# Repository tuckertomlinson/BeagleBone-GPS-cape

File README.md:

PCB layout for a GPS cape for the beaglebone black.

This is a home project. There is NO garauntee that the circuits do what
is intended, or that the function is adequately documented.

Any use of the files found in this project should be accompanied by a 
thorough review to determine proper function and fitness for use.

Project goals:
- clock discipline for the Beaglebone family such that a beaglebone with cape
	may act as an NTP stratum1 timeserver on a local network
- Use a GPS module to generate a 1 PPS signal that is synced to the atomic 
	clocks. The GPS module should interface with an active antenna so that
	good satellite lock may be attained indoors.
- provide an accurate RTC via a stand-alone i2c RTC module
- Hardware will be provided on a PCB cape, using SMT components for tight layout
	and low cost.
- Provide a hardware overlay file that may be enabled in uEnv.txt that will 
	automatically configure the correct pins for PPS capture, and RTC 
	connection

Stretch goals:
- Included a voltage regulated clock source, and force the BB to use the external 
	clock for better frequency stability

Current status:
- Proof of concept based on Adafruit Ultimate GPS breakout constructed and working
- 2 hardware capes designed
	- low cost cape based on Sierra Wireless XM1100 module
		- includeds RTC, and active antenna circuit
	- High cost cape based on uBlox LEA-M8T module
		- includes RTC, and 24Mhz VCTCXO clock. 
		- GPS module provides active antenna power
- Capes use Uart 4 to recieve GPS packets, and timer4 to take in PPS
- RTC is on i2c 1

Both capes completely untested.

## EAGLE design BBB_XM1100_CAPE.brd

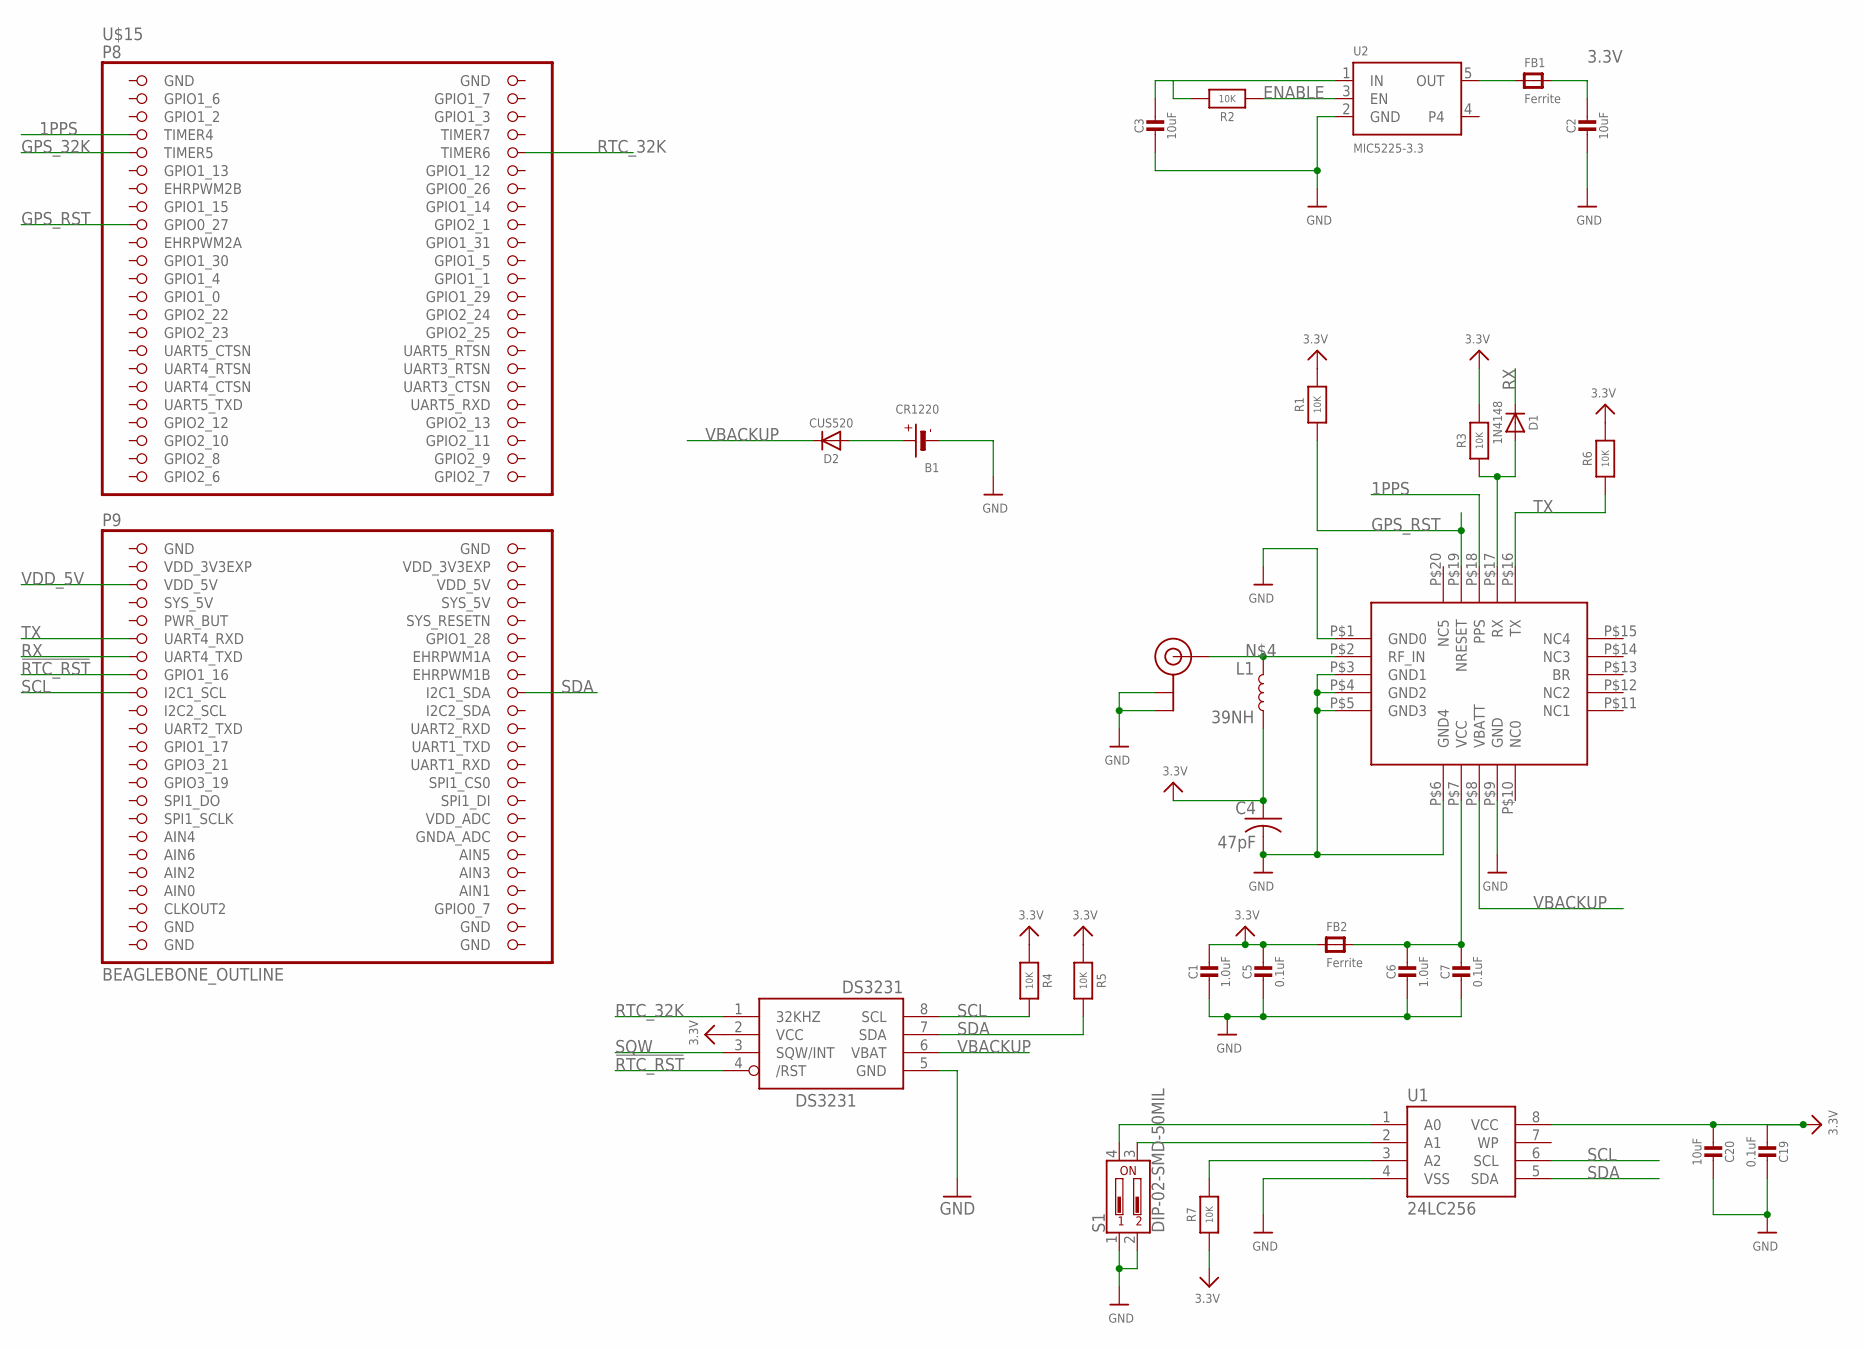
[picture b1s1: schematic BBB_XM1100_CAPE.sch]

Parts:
B1: CR1220
C1, C6: 1.0uF; 0805-NO
C2, C3, C20: 10uF; 0805-NO
C4: 47pF; C0805
C5, C7, C19: 0.1uF; 0805-NO
D1: 1N4148; SOD-323
D2: CUS520; SOD-323
DS3231: DS3231M-8PIN; SO08
FB1, FB2: Ferrite; 0805-NO@1
L1: 39NH; 0402
R1, R2, R3, R4, R5, R6, R7: 10K; 0805-NO
S1: DIP-02-SMD-50MIL; DIPSWITCH-02-50MIL
U1: 24LC256; SO08
U2: MIC5225-3.3; SOT23-5
U$3: XM1100
U$15: BEAGLEBONE_OUTLINE; BEAGLEBONE_SHIELD
U$20: U.FL

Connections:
1PPS: U$3.P$18 (PPS), U$15.7 (TIMER4)
3.3V: C1.1, C2.1, C4.1, C5.1, C19.1, C20.1, DS3231.2 (VCC), FB1.2, FB2.1, L1.2, R1.1, R3.1, R4.1, R5.1, R6.1, R7.1, U1.8 (VCC)
!RTC_RST: DS3231.4 (/RST), U$15.61 (GPIO1_16)
AIN0: U$15.85 (AIN0)
ENABLE: R2.1, U2.3 (EN)
GND: B1.-, C1.2, C2.2, C3.2, C4.2, C5.2, C6.2, C7.2, C19.2, C20.2, DS3231.5 (GND), S1.1, S1.2, U1.4 (VSS), U2.2 (GND), U$3.P$1 (GND0), U$3.P$3 (GND1), U$3.P$4 (GND2), U$3.P$5 (GND3), U$3.P$6 (GND4), U$3.P$9 (GND), U$15.1 (GND), U$15.2 (GND), U$15.47 (GND), U$15.48 (GND), U$15.89 (GND), U$15.90 (GND), U$15.91 (GND), U$15.92 (GND), U$20.P$1 (GND), U$20.P$2 (GND)
GPS_32K: U$15.9 (TIMER5)
GPS_RST: R1.2, U$3.P$19 (NRESET), U$15.17 (GPIO0_27)
unnamed: B1.+$1 (+), D2.A
unnamed: FB1.1, U2.5 (OUT)
unnamed: L1.1, U$3.P$2 (RF_IN), U$20.P$3 (SIGNAL)
unnamed: C6.1, C7.1, FB2.2, U$3.P$7 (VCC)
unnamed: R7.2, U1.3 (A2)
unnamed: S1.3, U1.2 (A1)
unnamed: S1.4, U1.1 (A0)
RTC_32K: DS3231.1 (32KHZ), U$15.10 (TIMER6)
RX: D1.C, U$15.59 (UART4_TXD)
RX_3V: D1.A, R3.2, U$3.P$17 (RX)
SCL: DS3231.8 (SCL), R4.2, U1.6 (SCL), U$15.63 (I2C1_SCL)
SDA: DS3231.7 (SDA), R5.2, U1.5 (SDA), U$15.64 (I2C1_SDA)
SQW: DS3231.3 (SQW/INT)
SYS_5V: U$15.53 (SYS_5V)
TX: R6.2, U$3.P$16 (TX), U$15.57 (UART4_RXD)
VBACKUP: D2.C, DS3231.6 (VBAT), U$3.P$8 (VBATT)
VDD_3V3EXP: U$15.49 (VDD_3V3EXP), U$15.50 (VDD_3V3EXP)
VDD_5V: C3.1, R2.2, U2.1 (IN), U$15.51 (VDD_5V), U$15.52 (VDD_5V)

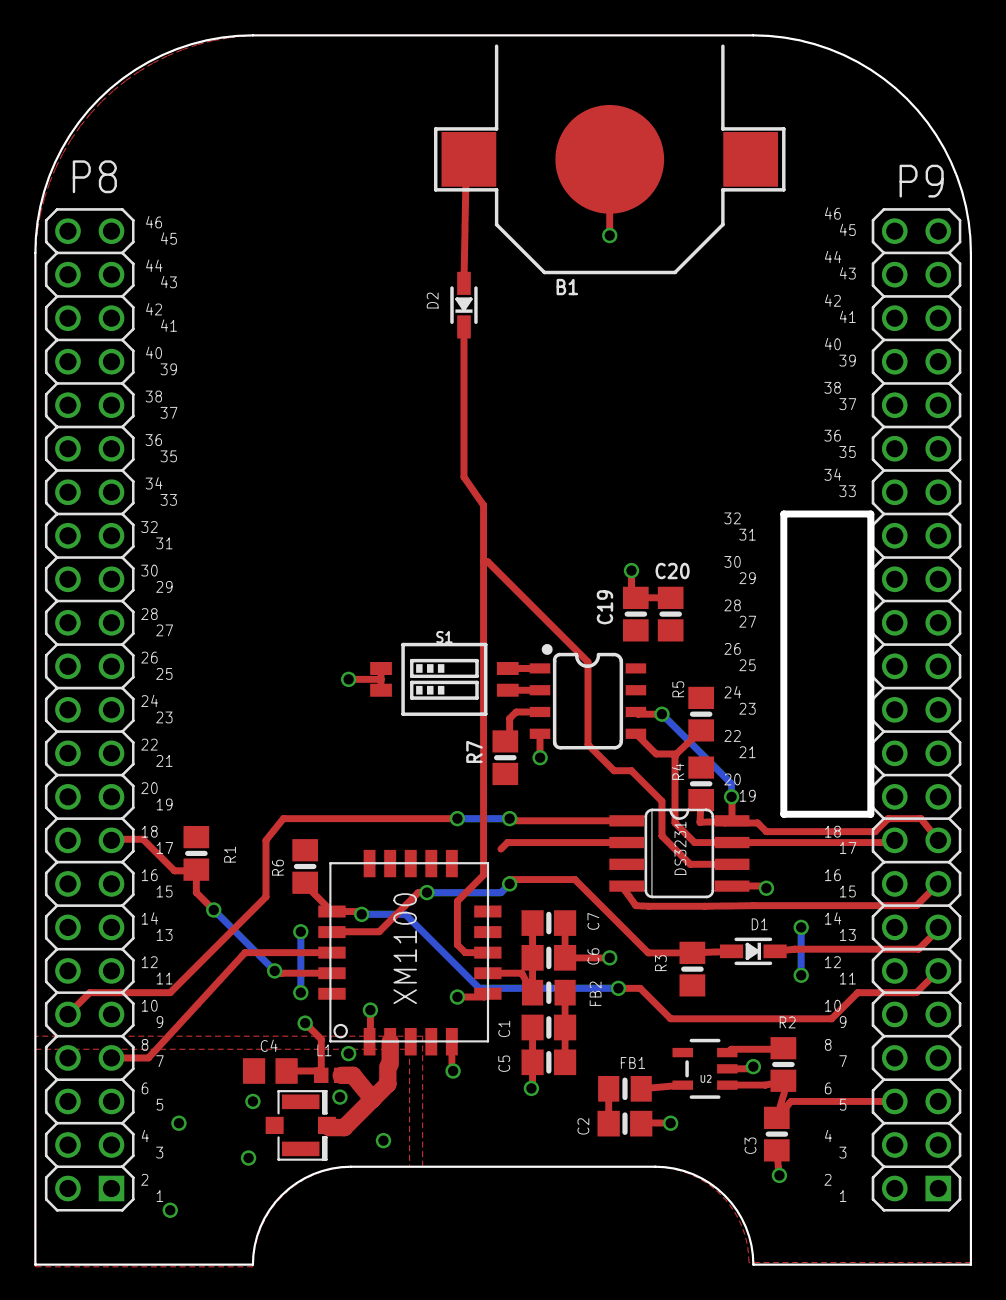
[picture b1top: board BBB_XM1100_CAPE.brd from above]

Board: 2 copper layers, 54.3 x 71.5 mm, 29 parts (0 on the bottom side), 22 nets.

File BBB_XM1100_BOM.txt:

BeagleBone LEA-M8T GPS timing cape BOM:
notes: 
1)almost no effort was given here to cost optimization. Caps and resistors may likely be substituted for alternative components at lower cost. 
2)cost reflects prices on Digikey as of the time that this BOM was compiled. Prices reflect single part quantity. discounts for bulk purchases are not taken into account

part: 			board ID			manuf		manuf. #		digikey#		cost Apr 2018 	link
GPS module		U$3				Sierra		XXM1100_1103874		 1645-1040-1-ND 	$12.98		https://www.digikey.com/product-detail/en/sierra-wireless/XM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		
10uF cap 0805		C1,C2,C3,C6			TDK		C2012X7R1A106K125AE 	445-173616-1-ND		$0.46		https://www.digikey.com/product-detail/en/tdk-corporation/C2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
0.1uF cap 0805		C5,C7				TDK		CGA4J2X8R1H104K125AA 	445-5909-1-ND 		$0.22		https://www.digikey.com/product-detail/en/tdk-corporation/CG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
47pF cap 0805		C4				ATC		600F470FT250XT  	1284-1061-1-ND 		$2.25		https://www.digikey.com/product-detail/en/american-technical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	
10kohm Resistor 0805	R1,R2,R3,R4,R5			Panasonic	ERA-6AEB103V		P10KDACT-ND 		$0.36		https://www.digikey.com/product-detail/en/panasonic-electron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
10 ohm Resistor 0805	R6				Vishay		TNPW080510R0FEEA	541-3916-1-ND 		$0.42		https://www.digikey.com/product-detail/en/vishay-dale/TNPW08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
Ferrite bead	0805	FB1,FB2				Laird		HI0805O121R-10		240-2393-1-ND		$0.11		https://www.digikey.com/product-detail/en/laird-signal-integ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
39nH inductor 0805	L1				Abracon		AISC-0805HQ-39NJ-T	535-12362-1-ND		$0.40		https://www.digikey.com/product-detail/en/murata-electronics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
3.3V regulator		U2				Microchip 	MIC5225-3.3		576-2980-1-ND 		$0.41		https://www.digikey.com/product-detail/en/microchip-technolo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
RTC			DS3231				Maxim		Ds3231MZ+		DS3231MZ+-ND		$7.72		https://www.digikey.com/product-detail/en/maxim-integrated/D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
U.FL Antenna jack	U$20				TE Connectivity	1909763-1 		 A118077CT-ND		$0.49		https://www.digikey.com/product-detail/en/te-connectivity-am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	
2X pinhdr 2x23		U$15				Samtec		SSQ-123-03-G-D		SAM1196-23-ND		$9.11		https://www.digikey.com/product-detail/en/samtec-inc/SSQ-123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  alt: https://www.adafruit.com/product/706
Diode			D1				Diodes Inc	1N4148WS-7-F		1N4148WS-FDICT-ND	$0.19		https://www.digikey.com/product-detail/en/diodes-incorporate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
Diode			D2				Toshiba		CUS520,H3F		CUS520H3FCT-ND		$0.22		https://www.digikey.com/product-detail/en/toshiba-semiconduc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
CR1220 batt. holder	B1				MPD		BK-885 			BK-885-ND		$0.35		https://www.digikey.com/products/en?keywords=3001k-nd

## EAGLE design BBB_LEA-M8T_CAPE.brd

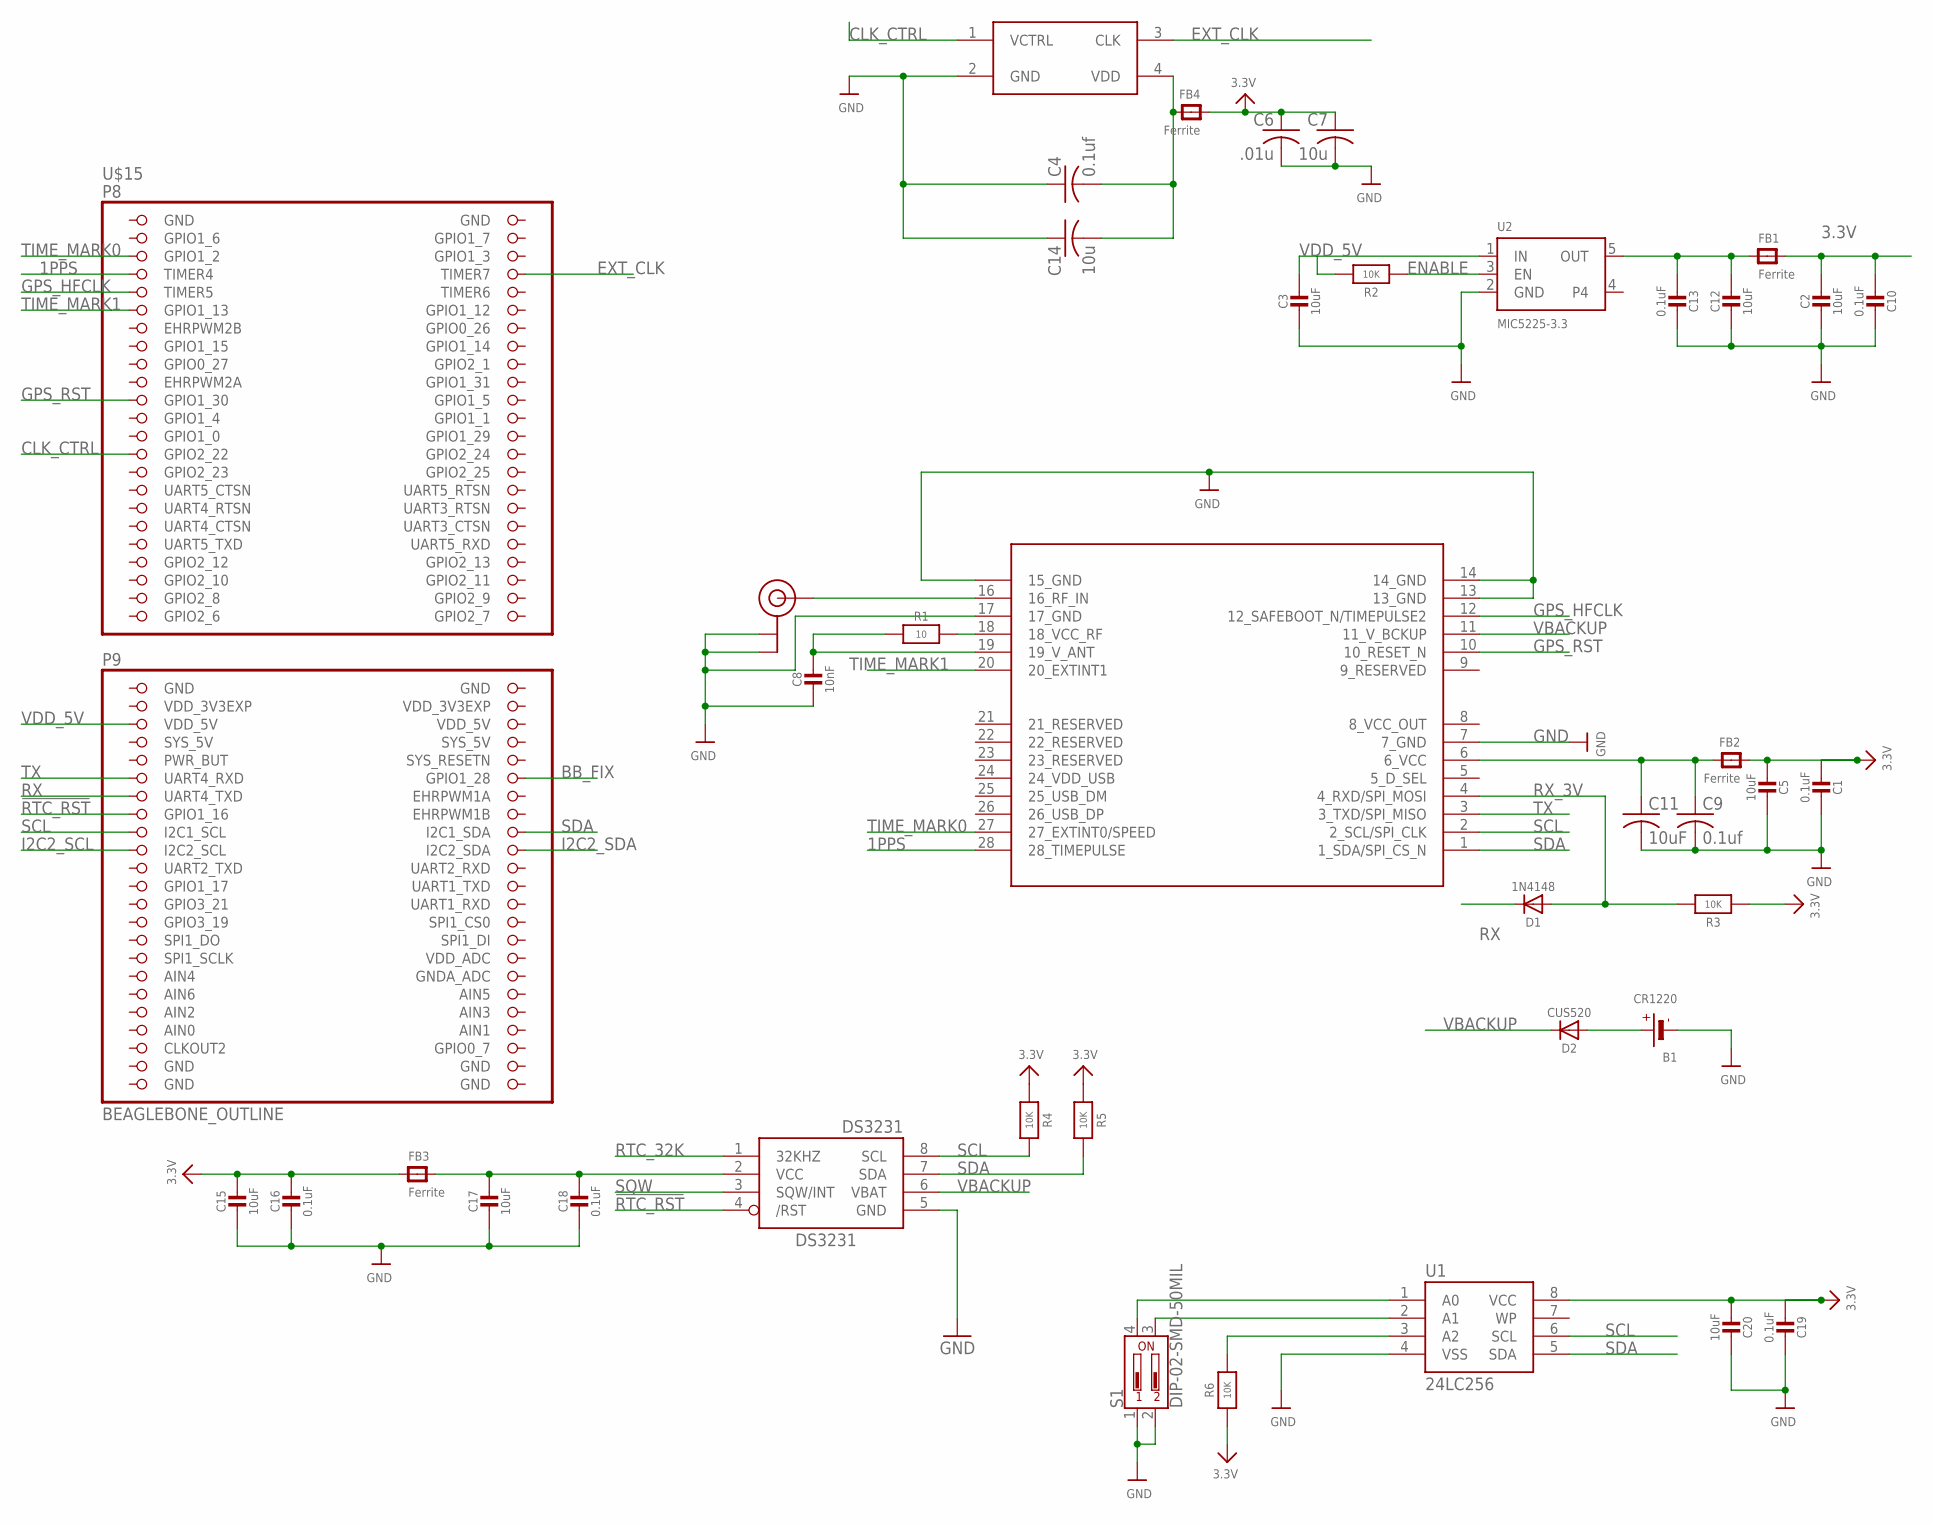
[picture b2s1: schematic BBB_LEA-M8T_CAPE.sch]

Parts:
B1: CR1220
C1, C10, C13, C16, C18, C19: 0.1uF; 0805-NO
C2, C3, C5, C12, C15, C17, C20: 10uF; 0805-NO
C4, C9: 0.1uf; C0805
C6: .01u; C0805
C7, C14: 10u; C0805
C8: 10nF; 0805-NO
C11: 10uF; C0805
D1: 1N4148; SOD-323
D2: CUS520; SOD-323
DS3231: DS3231M-8PIN; SO08
FB1, FB2, FB3, FB4: Ferrite; 0805-NO@1
R1: 10; 0805-NO
R2, R3, R4, R5, R6: 10K; 0805-NO
S1: DIP-02-SMD-50MIL; DIPSWITCH-02-50MIL
U1: 24LC256; SO08
U2: MIC5225-3.3; SOT23-5
U$1: LEA-M8
U$3: TAITIEN_TW-SERIES_OSCILLATOR
U$15: BEAGLEBONE_OUTLINE; BEAGLEBONE_SHIELD
U$20: U.FL

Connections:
1PPS: U$1.28 (28_TIMEPULSE), U$15.7 (TIMER4)
3.3V: C1.1, C2.1, C5.1, C6.1, C7.1, C10.1, C15.1, C16.1, C19.1, C20.1, FB1.2, FB2.1, FB3.1, FB4.1, R3.1, R4.1, R5.1, R6.1, U1.8 (VCC)
!RTC_RST: DS3231.4 (/RST), U$15.61 (GPIO1_16)
AIN0: U$15.85 (AIN0)
BB_FIX: U$15.58 (GPIO1_28)
CLK_CTRL: U$3.1 (VCTRL), U$15.27 (GPIO2_22)
ENABLE: R2.1, U2.3 (EN)
EXT_CLK: U$3.3 (CLK), U$15.8 (TIMER7)
GND: B1.-, C1.2, C2.2, C3.2, C4.1, C5.2, C6.2, C7.2, C8.2, C9.2, C10.2, C11.2, C12.2, C13.2, C14.1, C15.2, C16.2, C17.2, C18.2, C19.2, C20.2, DS3231.5 (GND), S1.1, S1.2, U1.4 (VSS), U2.2 (GND), U$1.7 (7_GND), U$1.13 (13_GND), U$1.14 (14_GND), U$1.15 (15_GND), U$1.17 (17_GND), U$3.2 (GND), U$15.1 (GND), U$15.2 (GND), U$15.47 (GND), U$15.48 (GND), U$15.89 (GND), U$15.90 (GND), U$15.91 (GND), U$15.92 (GND), U$20.P$1 (GND), U$20.P$2 (GND)
GPS_HFCLK: U$1.12 (12_SAFEBOOT_N/TIMEPULSE2), U$15.9 (TIMER5)
GPS_RST: U$1.10 (10_RESET_N), U$15.21 (GPIO1_30)
I2C2_SCL: U$15.65 (I2C2_SCL)
I2C2_SDA: U$15.66 (I2C2_SDA)
unnamed: B1.+$1 (+), D2.A
unnamed: C9.1, C11.1, FB2.2, U$1.6 (6_VCC)
unnamed: C12.1, C13.1, FB1.1, U2.5 (OUT)
unnamed: U$1.16 (16_RF_IN), U$20.P$3 (SIGNAL)
unnamed: C4.2, C14.2, FB4.2, U$3.4 (VDD)
unnamed: C17.1, C18.1, DS3231.2 (VCC), FB3.2
unnamed: R6.2, U1.3 (A2)
unnamed: S1.3, U1.2 (A1)
unnamed: S1.4, U1.1 (A0)
unnamed: R1.2, U$1.18 (18_VCC_RF)
unnamed: C8.1, R1.1, U$1.19 (19_V_ANT)
RTC_32K: DS3231.1 (32KHZ)
RX: D1.C, U$15.59 (UART4_TXD)
RX_3V: D1.A, R3.2, U$1.4 (4_RXD/SPI_MOSI)
SCL: DS3231.8 (SCL), R4.2, U1.6 (SCL), U$1.2 (2_SCL/SPI_CLK), U$15.63 (I2C1_SCL)
SDA: DS3231.7 (SDA), R5.2, U1.5 (SDA), U$1.1 (1_SDA/SPI_CS_N), U$15.64 (I2C1_SDA)
SQW: DS3231.3 (SQW/INT)
SYS_5V: U$15.53 (SYS_5V)
TIME_MARK0: U$1.27 (27_EXTINT0/SPEED), U$15.5 (GPIO1_2)
TIME_MARK1: U$1.20 (20_EXTINT1), U$15.11 (GPIO1_13)
TX: U$1.3 (3_TXD/SPI_MISO), U$15.57 (UART4_RXD)
VBACKUP: D2.C, DS3231.6 (VBAT), U$1.11 (11_V_BCKUP)
VDD_3V3EXP: U$15.49 (VDD_3V3EXP), U$15.50 (VDD_3V3EXP)
VDD_5V: C3.1, R2.2, U2.1 (IN), U$15.51 (VDD_5V), U$15.52 (VDD_5V)

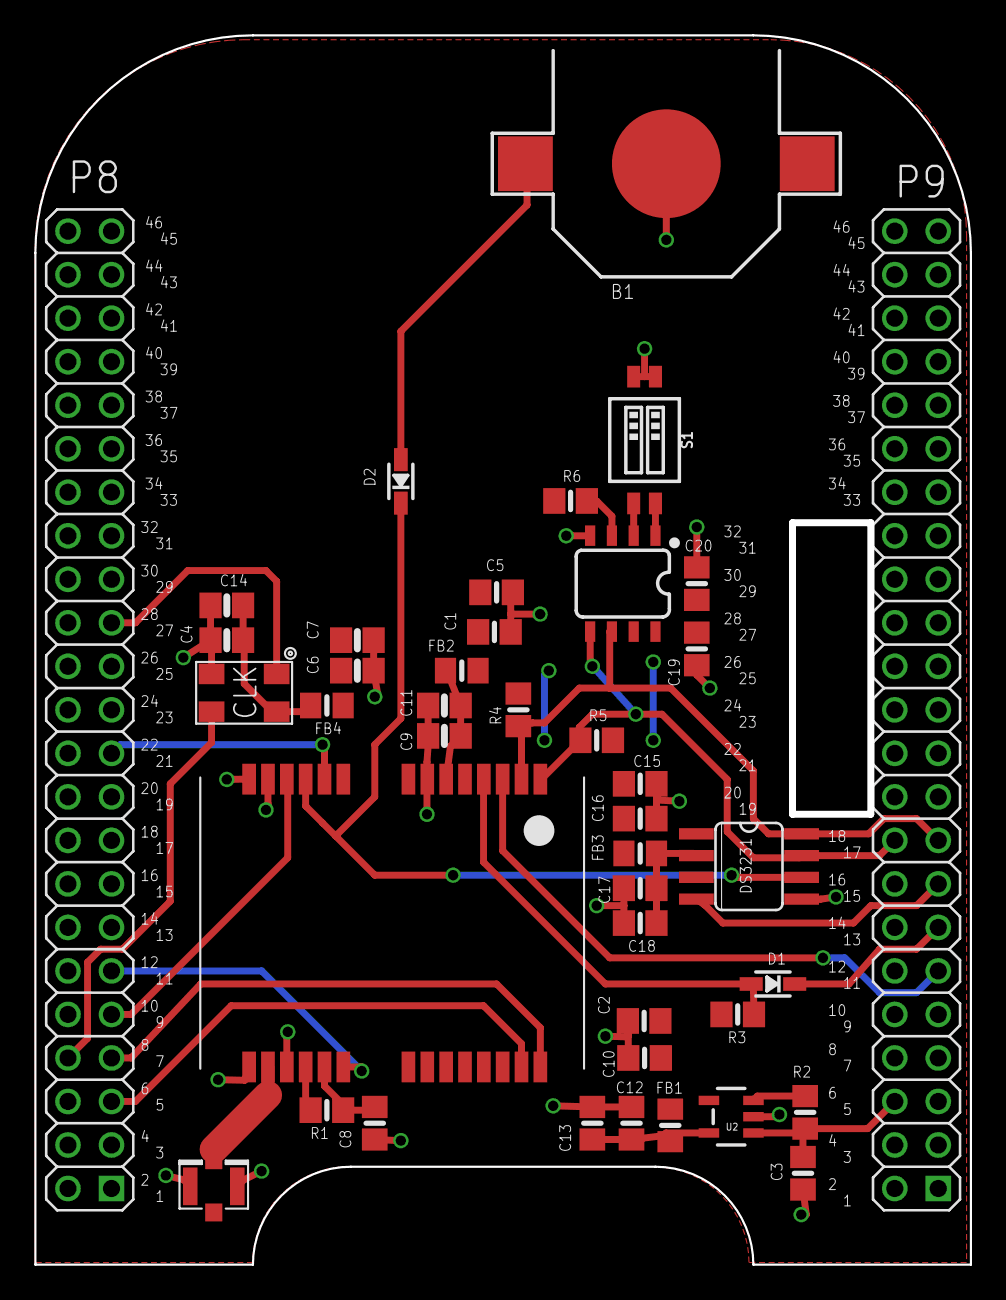
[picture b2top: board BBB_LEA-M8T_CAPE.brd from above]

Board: 2 copper layers, 54.3 x 71.5 mm, 41 parts (0 on the bottom side), 30 nets.

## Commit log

2018-04-01 initial commit. First pass at layout, and a readme
2018-04-01 readme formatting
2018-04-02 layout changes. Added filtering to LEA schematic. Added BOM for both schematics
2018-04-02 moved errant wire on XM1100 layout
2018-04-02 moved battery for cleaner layout on XM1100
2018-04-02 added gitignore to screen eagle autosave files
2018-04-02 deleted old autosave files
2018-04-12 BOM updates associated with populating first test boards
2018-04-13 minor updates to silkscreen layout to better match OSH Park silkscreen resolution
2018-04-13 minor layout and silkscreen cleanup
2018-04-26 added eeprom to ublox LEA cape
2018-04-26 added eeprom to XM1100 cape
2018-05-09 corrected error in VCC/GND connections on xm1100 cape

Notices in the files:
parts and their libraries:
SparkFun-IC-Memory: Licensing: Creative Commons ShareAlike 4.0 International - https://creativecommons.org/licenses/by-sa/4.0
